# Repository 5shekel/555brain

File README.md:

555brain
========

555 based brain module

watch the video! > 

via http://www.reddit.com/r/electronics/comments/fsjno/simple_555_timer_based_servo_controllers_for/  
orginal design by Tom Jenner based on work by B.E.A.M robotics community and Mark Tilden et al

555brain thru-hole branch, cut on copper foil in TAMI.org.il

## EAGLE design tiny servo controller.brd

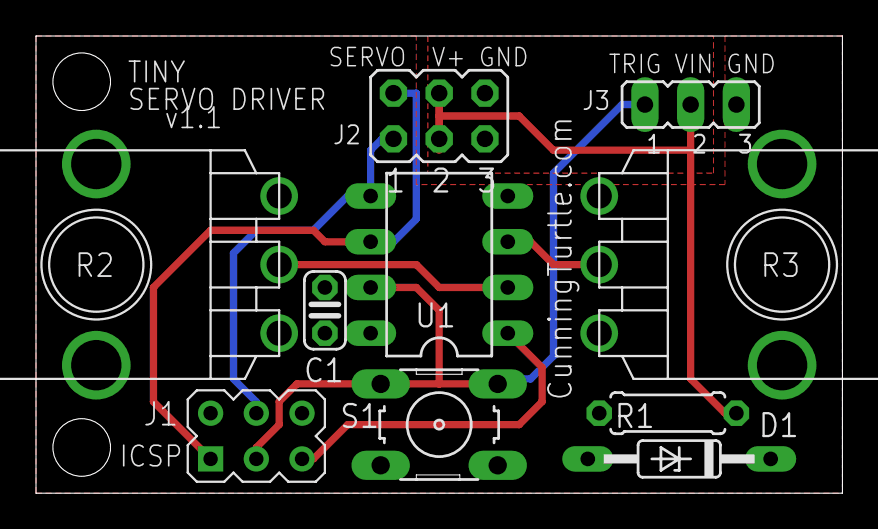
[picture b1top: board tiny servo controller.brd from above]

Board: 2 copper layers, 44.8 x 25.4 mm, 10 parts (0 on the bottom side), 9 nets.

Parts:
C1: 0.1uF; C025-024X044
D1: 5.1V; DO35Z10
J1: AVR_SPI_PRG; AVR_ISP_6P
J2: JP3Q
J3: JP2
R1: 33; 0207/7
R2, R3: CT2265-ND
S1: TACTILE_6MM
U1: ATTINY85DIL08; DIL08

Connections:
GND: C1.2, D1.A, J1.6, J2.5, J2.6, J3.3, R2.3, R3.3, S1.3, S1.4, U1.4
MISO/PWM2: J1.1, J2.2, U1.6
MOSI/PWM1: J1.4, J2.1, U1.5
POT1: R2.2, U1.2
POT2: R3.2, U1.3
RESET_N: J1.5, U1.1
SCK/SWITCH: J1.3, J3.1, S1.1, S1.2, U1.7
V+: J2.3, J2.4, J3.2, R1.1
VCC: C1.1, D1.C, J1.2, R1.2, R2.1, R3.1, U1.8

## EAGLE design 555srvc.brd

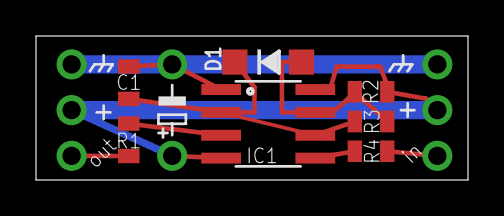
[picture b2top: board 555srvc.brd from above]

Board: 2 copper layers, 24.0 x 8.0 mm, 11 parts (1 on the bottom side), 8 nets.

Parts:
C1: 1uF; 0805
C2: E5-6
D1: SOD-123
IC1: 555; SO08
JP2: SERVO_OUT; 1X03-CLEANBIG
JP3: INPUT / CV; 1X03-CLEANBIG
R1: 2.2k; 0805
R2: 1.5k; 0805
R3: 47k; 0805
R4: 15k; 0805
U$5: OSHW_6X100_NOTEXT

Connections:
GND: C1.2, C2.-, IC1.1, JP2.1, JP3.1
INPUT: JP3.3, R4.2
unnamed: C1.1, D1.C, IC1.2, IC1.6, R3.1
unnamed: D1.A, IC1.7, R2.2, R3.2
unnamed: IC1.5, R4.1
unnamed: IC1.3, R1.1
SERVO_OUT: JP2.3, R1.2
VCC: C2.+, IC1.4, IC1.8, JP2.2, JP3.2, R2.1

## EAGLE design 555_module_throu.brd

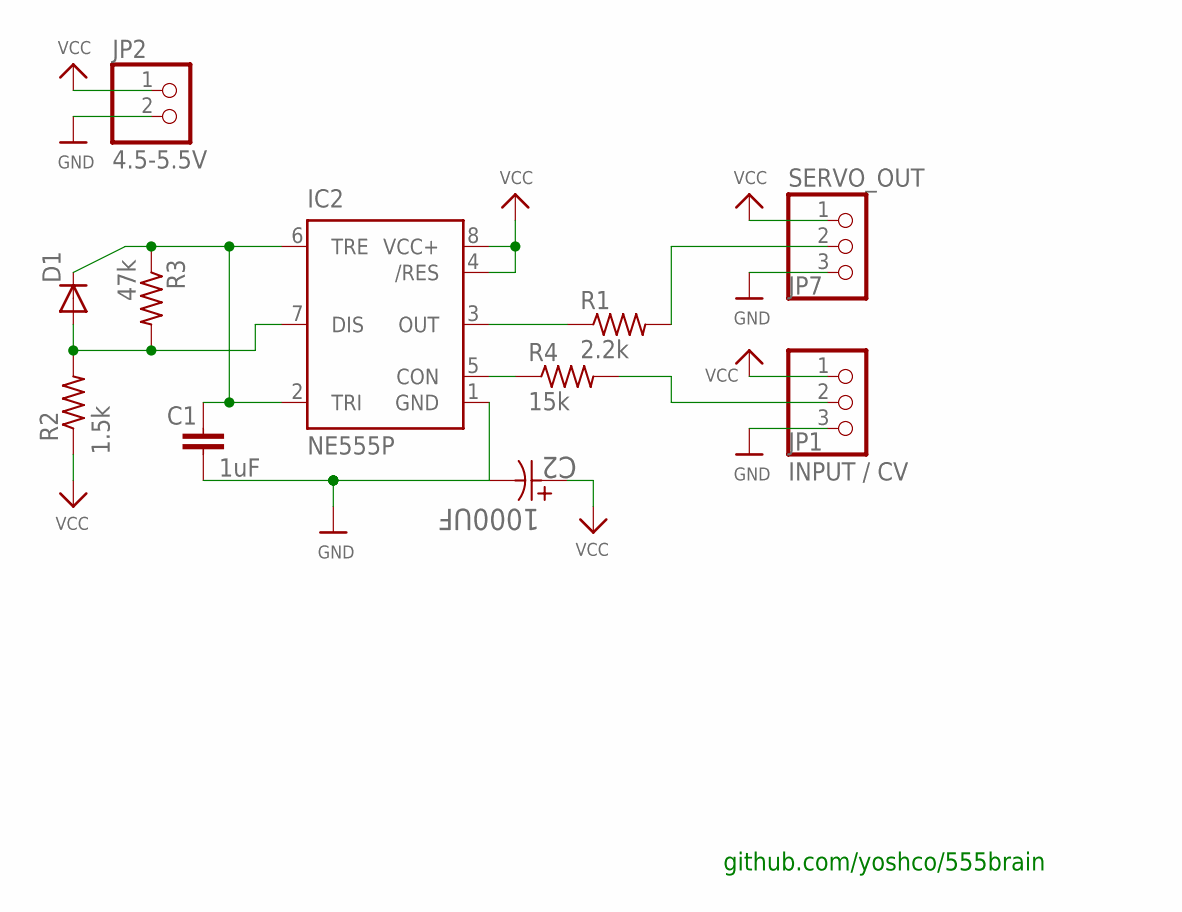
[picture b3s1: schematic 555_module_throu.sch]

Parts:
C1: 1uF; AXIAL-5MM
C2: 1000UF; CAPPR500-1000X3200
D1: 1N4004; DO41-10
IC2: NE555P; DIL-08
JP1: INPUT / CV; 1X03
JP2: 4.5-5.5V; 1X02_OVAL
JP7: SERVO_OUT; 1X03
R1: 2.2k; 0204/7
R2: 1.5k; 0204/7
R3: 47k; 0204/7
R4: 15k; 0204/7

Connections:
GND: C1.P$2 (2), C2.2, IC2.1 (GND), JP1.3, JP2.2, JP7.3
INPUT: JP1.2, R4.2
unnamed: C1.P$1 (1), D1.C, IC2.2 (TRI), IC2.6 (TRE), R3.1
unnamed: D1.A, IC2.7 (DIS), R2.2, R3.2
unnamed: IC2.5 (CON), R4.1
unnamed: IC2.3 (OUT), R1.1
SERVO_OUT: JP7.2, R1.2
VCC: C2.1, IC2.4 (/RES), IC2.8 (VCC+), JP1.1, JP2.1, JP7.1, R2.1

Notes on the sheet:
github.com/yoshco/555brain

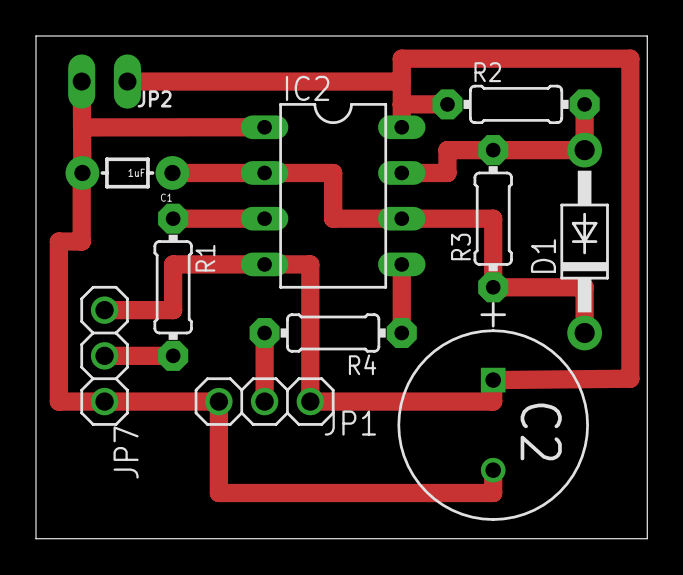
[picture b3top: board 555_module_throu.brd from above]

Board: 2 copper layers, 34.0 x 27.9 mm, 11 parts (0 on the bottom side), 8 nets.

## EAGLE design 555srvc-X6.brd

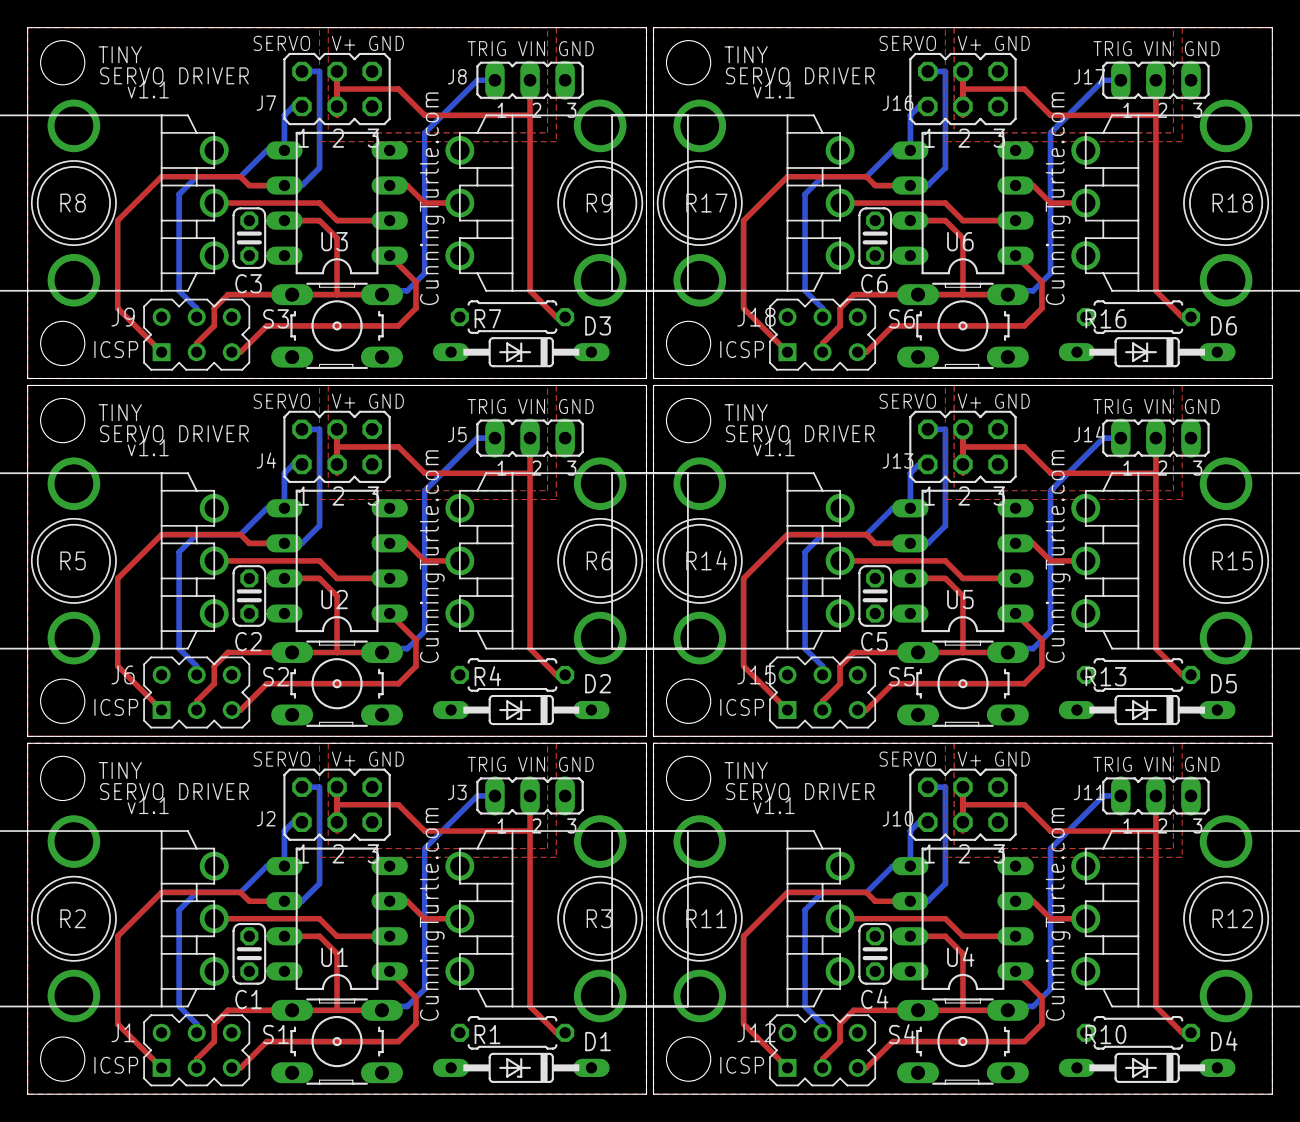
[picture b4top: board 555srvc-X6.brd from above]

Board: 2 copper layers, 90.1 x 77.2 mm, 60 parts (0 on the bottom side), 54 nets.

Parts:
C1, C2, C3, C4, C5, C6: 0.1uF; C025-024X044
D1, D2, D3, D4, D5, D6: 5.1V; DO35Z10
J1, J6, J9, J12, J15, J18: AVR_SPI_PRG; AVR_ISP_6P
J2, J4, J7, J10, J13, J16: JP3Q
J3, J5, J8, J11, J14, J17: JP2
R1, R4, R7, R10, R13, R16: 33; 0207/7
R2, R3, R5, R6, R8, R9, R11, R12, R14, R15, R17, R18: CT2265-ND
S1, S2, S3, S4, S5, S6: TACTILE_6MM
U1, U2, U3, U4, U5, U6: ATTINY85DIL08; DIL08

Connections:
GND: C1.2, D1.A, J1.6, J2.5, J2.6, J3.3, R2.3, R3.3, S1.3, S1.4, U1.4
GND1: C2.2, D2.A, J4.5, J4.6, J5.3, J6.6, R5.3, R6.3, S2.3, S2.4, U2.4
GND2: C3.2, D3.A, J7.5, J7.6, J8.3, J9.6, R8.3, R9.3, S3.3, S3.4, U3.4
GND3: C4.2, D4.A, J10.5, J10.6, J11.3, J12.6, R11.3, R12.3, S4.3, S4.4, U4.4
GND4: C5.2, D5.A, J13.5, J13.6, J14.3, J15.6, R14.3, R15.3, S5.3, S5.4, U5.4
GND5: C6.2, D6.A, J16.5, J16.6, J17.3, J18.6, R17.3, R18.3, S6.3, S6.4, U6.4
MISO/PWM1: J4.2, J6.1, U2.6
MISO/PWM2: J1.1, J2.2, U1.6
MISO/PWM3: J7.2, J9.1, U3.6
MISO/PWM4: J10.2, J12.1, U4.6
MISO/PWM5: J13.2, J15.1, U5.6
MISO/PWM6: J16.2, J18.1, U6.6
MOSI/PWM1: J1.4, J2.1, U1.5
MOSI/PWM2: J4.1, J6.4, U2.5
MOSI/PWM3: J7.1, J9.4, U3.5
MOSI/PWM4: J10.1, J12.4, U4.5
MOSI/PWM5: J13.1, J15.4, U5.5
MOSI/PWM6: J16.1, J18.4, U6.5
POT1: R2.2, U1.2
POT2: R3.2, U1.3
POT3: R5.2, U2.2
POT4: R6.2, U2.3
POT5: R8.2, U3.2
POT6: R9.2, U3.3
POT7: R11.2, U4.2
POT8: R12.2, U4.3
POT9: R14.2, U5.2
POT10: R15.2, U5.3
POT11: R17.2, U6.2
POT12: R18.2, U6.3
RESET_N: J1.5, U1.1
RESET_N1: J6.5, U2.1
RESET_N2: J9.5, U3.1
RESET_N3: J12.5, U4.1
RESET_N4: J15.5, U5.1
RESET_N5: J18.5, U6.1
SCK/SWITCH: J1.3, J3.1, S1.1, S1.2, U1.7
SCK/SWITCH1: J5.1, J6.3, S2.1, S2.2, U2.7
SCK/SWITCH2: J8.1, J9.3, S3.1, S3.2, U3.7
SCK/SWITCH3: J11.1, J12.3, S4.1, S4.2, U4.7
SCK/SWITCH4: J14.1, J15.3, S5.1, S5.2, U5.7
SCK/SWITCH5: J17.1, J18.3, S6.1, S6.2, U6.7
V+: J2.3, J2.4, J3.2, R1.1
V+1: J4.3, J4.4, J5.2, R4.1
V+2: J7.3, J7.4, J8.2, R7.1
V+3: J10.3, J10.4, J11.2, R10.1
V+4: J13.3, J13.4, J14.2, R13.1
V+5: J16.3, J16.4, J17.2, R16.1
VCC: C1.1, D1.C, J1.2, R1.2, R2.1, R3.1, U1.8
VCC1: C2.1, D2.C, J6.2, R4.2, R5.1, R6.1, U2.8
VCC2: C3.1, D3.C, J9.2, R7.2, R8.1, R9.1, U3.8
VCC3: C4.1, D4.C, J12.2, R10.2, R11.1, R12.1, U4.8
VCC4: C5.1, D5.C, J15.2, R13.2, R14.1, R15.1, U5.8
VCC5: C6.1, D6.C, J18.2, R16.2, R17.1, R18.1, U6.8

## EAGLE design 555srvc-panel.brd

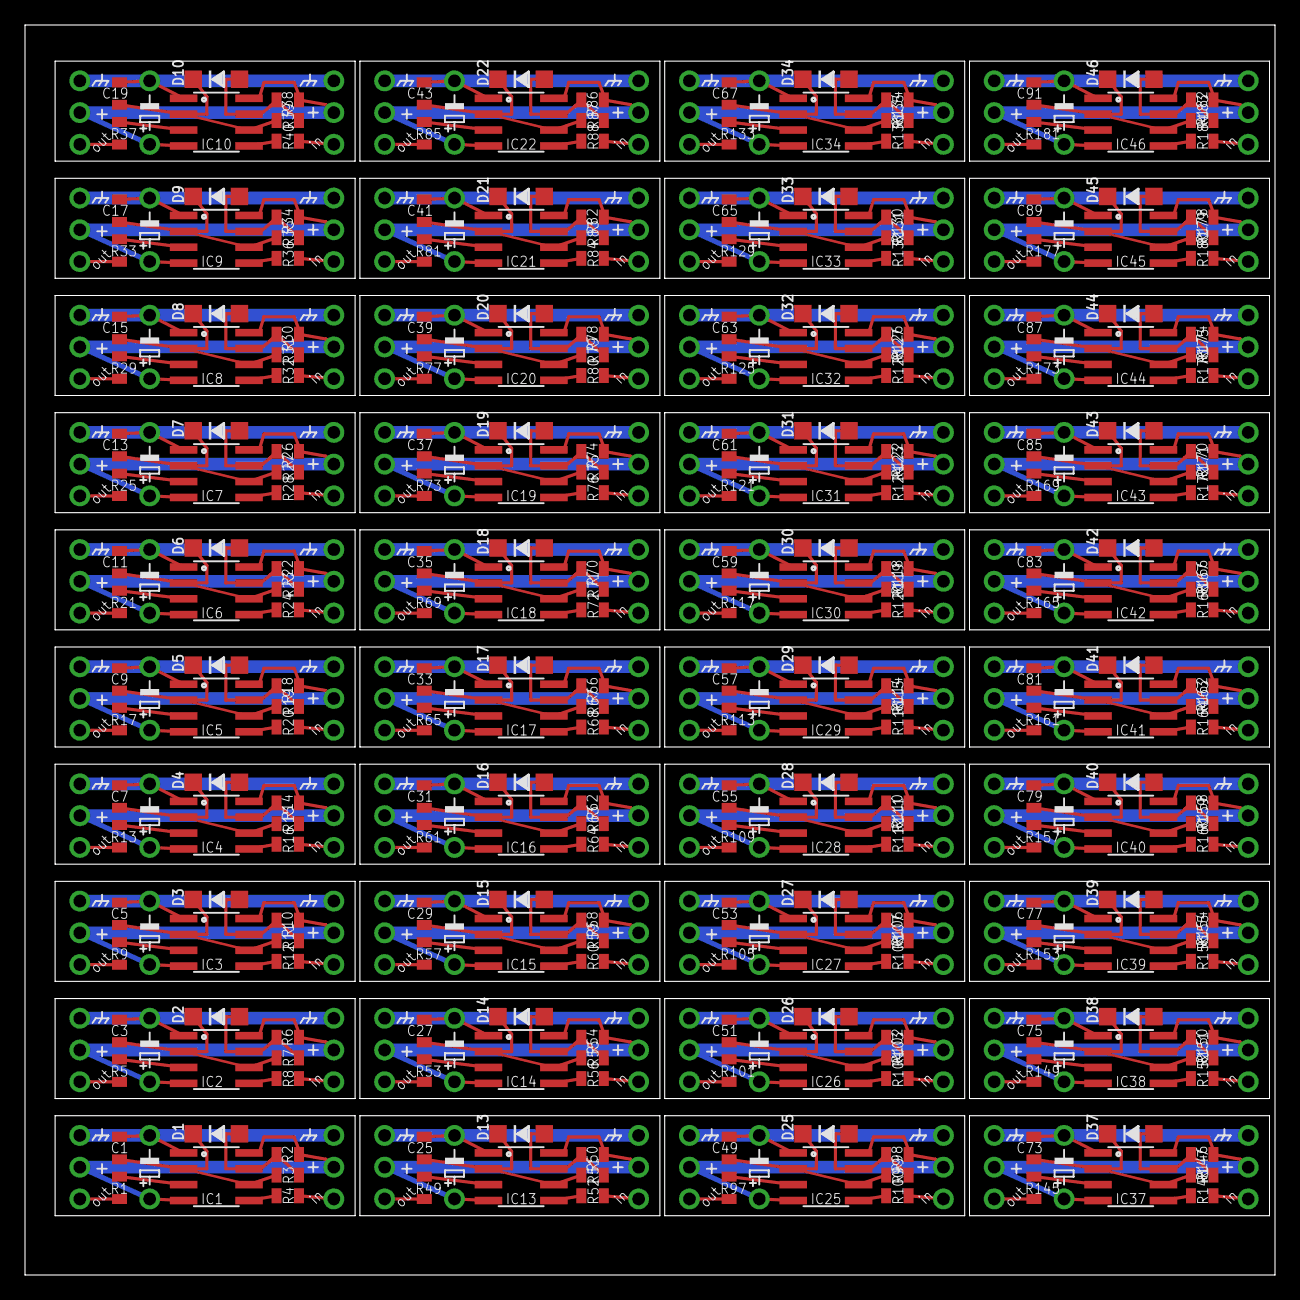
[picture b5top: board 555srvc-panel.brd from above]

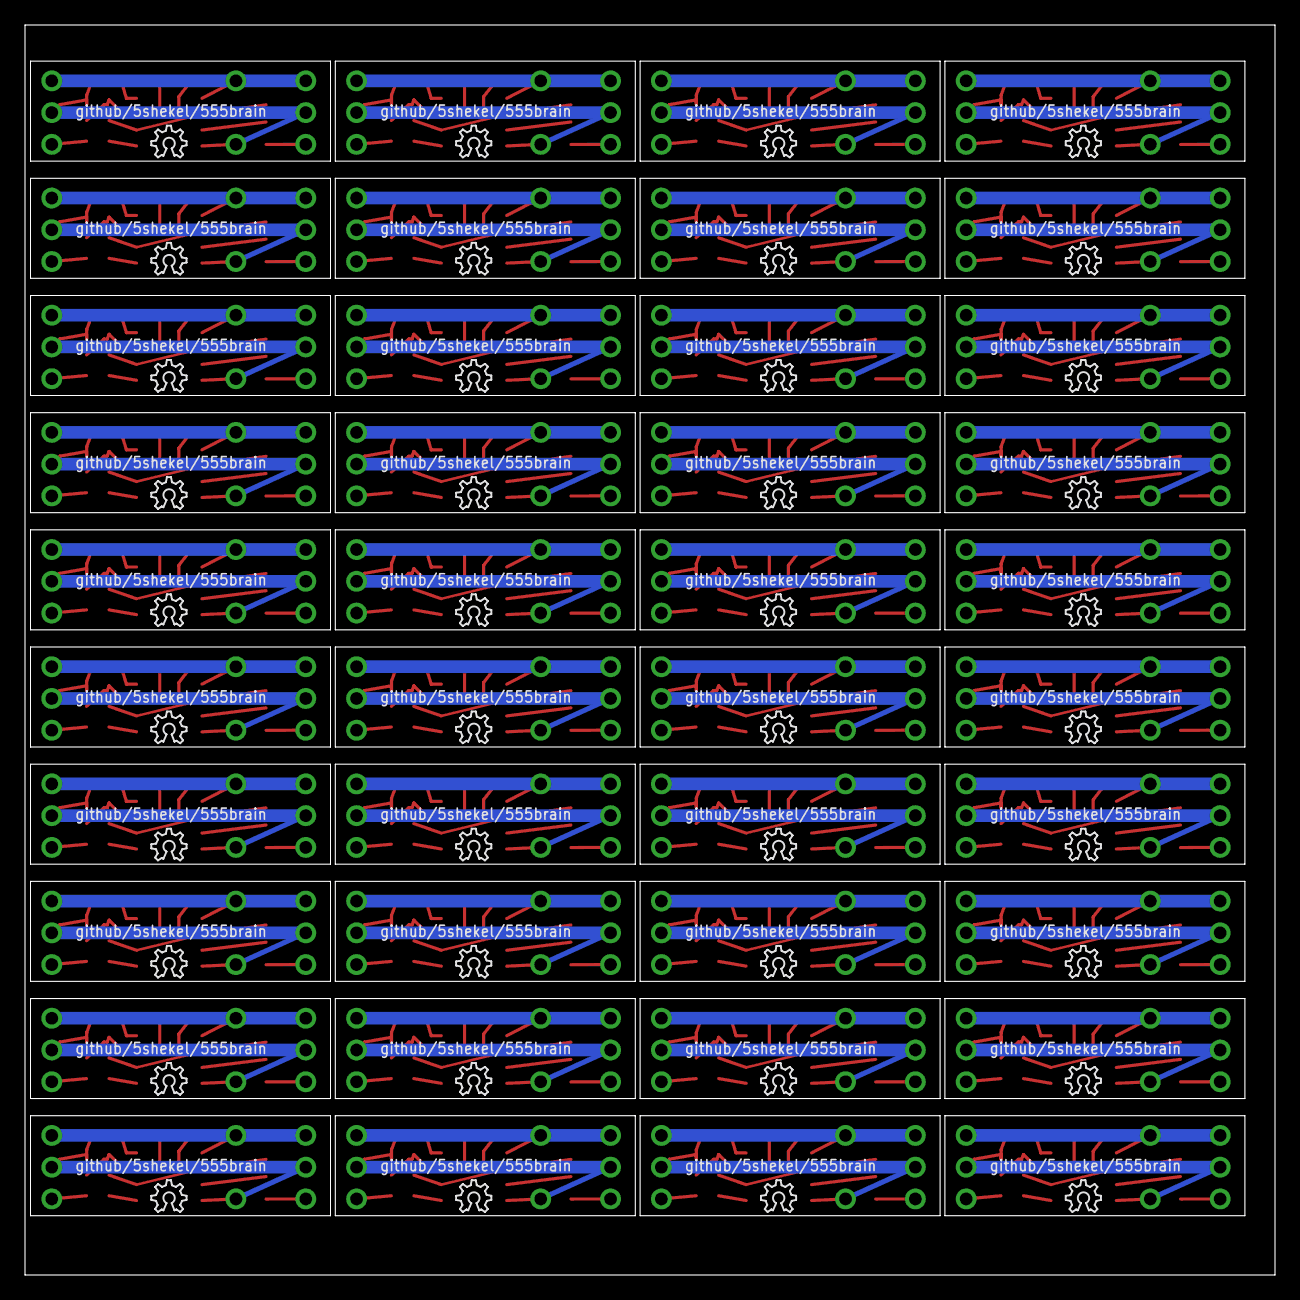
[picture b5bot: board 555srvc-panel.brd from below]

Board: 2 copper layers, 100.0 x 100.0 mm, 440 parts (40 on the bottom side), 320 nets.

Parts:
C1, C3, C5, C7, C9, C11, C13, C15, C17, C19, C25, C27, C29, C31, C33, C35, C37, C39, C41, C43, C49, C51, C53, C55, C57, C59, C61, C63, C65, C67, C73, C75, C77, C79, C81, C83, C85, C87, C89, C91: 1uF; 0805
C2, C4, C6, C8, C10, C12, C14, C16, C18, C20, C26, C28, C30, C32, C34, C36, C38, C40, C42, C44, C50, C52, C54, C56, C58, C60, C62, C64, C66, C68, C74, C76, C78, C80, C82, C84, C86, C88, C90, C92: E5-6
D1, D2, D3, D4, D5, D6, D7, D8, D9, D10, D13, D14, D15, D16, D17, D18, D19, D20, D21, D22, D25, D26, D27, D28, D29, D30, D31, D32, D33, D34, D37, D38, D39, D40, D41, D42, D43, D44, D45, D46: SOD-123
IC1, IC2, IC3, IC4, IC5, IC6, IC7, IC8, IC9, IC10, IC13, IC14, IC15, IC16, IC17, IC18, IC19, IC20, IC21, IC22, IC25, IC26, IC27, IC28, IC29, IC30, IC31, IC32, IC33, IC34, IC37, IC38, IC39, IC40, IC41, IC42, IC43, IC44, IC45, IC46: 555; SO08
JP1, JP2, JP5, JP7, JP9, JP11, JP13, JP15, JP17, JP19, JP25, JP27, JP29, JP31, JP33, JP35, JP37, JP39, JP41, JP43, JP49, JP51, JP53, JP55, JP57, JP59, JP61, JP63, JP65, JP67, JP73, JP75, JP77, JP79, JP81, JP83, JP85, JP87, JP89, JP91: SERVO_OUT; 1X03-CLEANBIG
JP3, JP4, JP6, JP8, JP10, JP12, JP14, JP16, JP18, JP20, JP26, JP28, JP30, JP32, JP34, JP36, JP38, JP40, JP42, JP44, JP50, JP52, JP54, JP56, JP58, JP60, JP62, JP64, JP66, JP68, JP74, JP76, JP78, JP80, JP82, JP84, JP86, JP88, JP90, JP92: INPUT / CV; 1X03-CLEANBIG
R1, R5, R9, R13, R17, R21, R25, R29, R33, R37, R49, R53, R57, R61, R65, R69, R73, R77, R81, R85, R97, R101, R105, R109, R113, R117, R121, R125, R129, R133, R145, R149, R153, R157, R161, R165, R169, R173, R177, R181: 2.2k; 0805
R2, R6, R10, R14, R18, R22, R26, R30, R34, R38, R50, R54, R58, R62, R66, R70, R74, R78, R82, R86, R98, R102, R106, R110, R114, R118, R122, R126, R130, R134, R146, R150, R154, R158, R162, R166, R170, R174, R178, R182: 1.5k; 0805
R3, R7, R11, R15, R19, R23, R27, R31, R35, R39, R51, R55, R59, R63, R67, R71, R75, R79, R83, R87, R99, R103, R107, R111, R115, R119, R123, R127, R131, R135, R147, R151, R155, R159, R163, R167, R171, R175, R179, R183: 47k; 0805
R4, R8, R12, R16, R20, R24, R28, R32, R36, R40, R52, R56, R60, R64, R68, R72, R76, R80, R84, R88, R100, R104, R108, R112, R116, R120, R124, R128, R132, R136, R148, R152, R156, R160, R164, R168, R172, R176, R180, R184: 15k; 0805
U$1, U$2, U$3, U$4, U$5, U$6, U$7, U$8, U$9, U$10, U$13, U$14, U$15, U$16, U$17, U$18, U$19, U$20, U$21, U$22, U$25, U$26, U$27, U$28, U$29, U$30, U$31, U$32, U$33, U$34, U$37, U$38, U$39, U$40, U$41, U$42, U$43, U$44, U$45, U$46: OSHW_6X100_NOTEXT

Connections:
GND: C1.2, C2.-, IC1.1, JP2.1, JP3.1
GND1: C3.2, C4.-, IC2.1, JP1.1, JP4.1
GND2: C5.2, C6.-, IC3.1, JP5.1, JP6.1
GND3: C7.2, C8.-, IC4.1, JP7.1, JP8.1
GND4: C9.2, C10.-, IC5.1, JP9.1, JP10.1
GND5: C11.2, C12.-, IC6.1, JP11.1, JP12.1
GND6: C13.2, C14.-, IC7.1, JP13.1, JP14.1
GND7: C15.2, C16.-, IC8.1, JP15.1, JP16.1
GND8: C17.2, C18.-, IC9.1, JP17.1, JP18.1
GND9: C19.2, C20.-, IC10.1, JP19.1, JP20.1
GND12: C25.2, C26.-, IC13.1, JP25.1, JP26.1
GND13: C27.2, C28.-, IC14.1, JP27.1, JP28.1
GND14: C29.2, C30.-, IC15.1, JP29.1, JP30.1
GND15: C31.2, C32.-, IC16.1, JP31.1, JP32.1
GND16: C33.2, C34.-, IC17.1, JP33.1, JP34.1
GND17: C35.2, C36.-, IC18.1, JP35.1, JP36.1
GND18: C37.2, C38.-, IC19.1, JP37.1, JP38.1
GND19: C39.2, C40.-, IC20.1, JP39.1, JP40.1
GND20: C41.2, C42.-, IC21.1, JP41.1, JP42.1
GND21: C43.2, C44.-, IC22.1, JP43.1, JP44.1
GND24: C49.2, C50.-, IC25.1, JP49.1, JP50.1
GND25: C51.2, C52.-, IC26.1, JP51.1, JP52.1
GND26: C53.2, C54.-, IC27.1, JP53.1, JP54.1
GND27: C55.2, C56.-, IC28.1, JP55.1, JP56.1
GND28: C57.2, C58.-, IC29.1, JP57.1, JP58.1
GND29: C59.2, C60.-, IC30.1, JP59.1, JP60.1
GND30: C61.2, C62.-, IC31.1, JP61.1, JP62.1
GND31: C63.2, C64.-, IC32.1, JP63.1, JP64.1
GND32: C65.2, C66.-, IC33.1, JP65.1, JP66.1
GND33: C67.2, C68.-, IC34.1, JP67.1, JP68.1
GND36: C73.2, C74.-, IC37.1, JP73.1, JP74.1
GND37: C75.2, C76.-, IC38.1, JP75.1, JP76.1
GND38: C77.2, C78.-, IC39.1, JP77.1, JP78.1
GND39: C79.2, C80.-, IC40.1, JP79.1, JP80.1
GND40: C81.2, C82.-, IC41.1, JP81.1, JP82.1
GND41: C83.2, C84.-, IC42.1, JP83.1, JP84.1
GND42: C85.2, C86.-, IC43.1, JP85.1, JP86.1
GND43: C87.2, C88.-, IC44.1, JP87.1, JP88.1
GND44: C89.2, C90.-, IC45.1, JP89.1, JP90.1
GND45: C91.2, C92.-, IC46.1, JP91.1, JP92.1
INPUT: JP3.3, R4.2
INPUT1: JP4.3, R8.2
INPUT2: JP6.3, R12.2
INPUT3: JP8.3, R16.2
INPUT4: JP10.3, R20.2
INPUT5: JP12.3, R24.2
INPUT6: JP14.3, R28.2
INPUT7: JP16.3, R32.2
INPUT8: JP18.3, R36.2
INPUT9: JP20.3, R40.2
INPUT12: JP26.3, R52.2
INPUT13: JP28.3, R56.2
INPUT14: JP30.3, R60.2
INPUT15: JP32.3, R64.2
INPUT16: JP34.3, R68.2
INPUT17: JP36.3, R72.2
INPUT18: JP38.3, R76.2
INPUT19: JP40.3, R80.2
INPUT20: JP42.3, R84.2
INPUT21: JP44.3, R88.2
INPUT24: JP50.3, R100.2
INPUT25: JP52.3, R104.2
INPUT26: JP54.3, R108.2
INPUT27: JP56.3, R112.2
INPUT28: JP58.3, R116.2
INPUT29: JP60.3, R120.2
INPUT30: JP62.3, R124.2
INPUT31: JP64.3, R128.2
INPUT32: JP66.3, R132.2
INPUT33: JP68.3, R136.2
INPUT36: JP74.3, R148.2
INPUT37: JP76.3, R152.2
INPUT38: JP78.3, R156.2
INPUT39: JP80.3, R160.2
INPUT40: JP82.3, R164.2
INPUT41: JP84.3, R168.2
INPUT42: JP86.3, R172.2
INPUT43: JP88.3, R176.2
INPUT44: JP90.3, R180.2
INPUT45: JP92.3, R184.2
unnamed: C1.1, D1.C, IC1.2, IC1.6, R3.1
unnamed: D1.A, IC1.7, R2.2, R3.2
unnamed: C3.1, D2.C, IC2.2, IC2.6, R7.1
unnamed: IC1.5, R4.1
unnamed: IC1.3, R1.1
unnamed: D2.A, IC2.7, R6.2, R7.2
unnamed: IC2.5, R8.1
unnamed: IC2.3, R5.1
unnamed: C5.1, D3.C, IC3.2, IC3.6, R11.1
unnamed: D3.A, IC3.7, R10.2, R11.2
unnamed: IC3.5, R12.1
unnamed: IC3.3, R9.1
unnamed: C7.1, D4.C, IC4.2, IC4.6, R15.1
unnamed: D4.A, IC4.7, R14.2, R15.2
unnamed: IC4.5, R16.1
unnamed: IC4.3, R13.1
unnamed: C9.1, D5.C, IC5.2, IC5.6, R19.1
unnamed: D5.A, IC5.7, R18.2, R19.2
unnamed: IC5.5, R20.1
unnamed: IC5.3, R17.1
unnamed: C11.1, D6.C, IC6.2, IC6.6, R23.1
unnamed: D6.A, IC6.7, R22.2, R23.2
unnamed: IC6.5, R24.1
unnamed: IC6.3, R21.1
unnamed: C13.1, D7.C, IC7.2, IC7.6, R27.1
unnamed: D7.A, IC7.7, R26.2, R27.2
unnamed: IC7.5, R28.1
unnamed: IC7.3, R25.1
unnamed: C15.1, D8.C, IC8.2, IC8.6, R31.1
unnamed: D8.A, IC8.7, R30.2, R31.2
unnamed: IC8.5, R32.1
unnamed: IC8.3, R29.1
unnamed: C17.1, D9.C, IC9.2, IC9.6, R35.1
unnamed: D9.A, IC9.7, R34.2, R35.2
unnamed: IC9.5, R36.1
unnamed: IC9.3, R33.1
unnamed: C19.1, D10.C, IC10.2, IC10.6, R39.1
unnamed: D10.A, IC10.7, R38.2, R39.2
unnamed: IC10.5, R40.1
unnamed: IC10.3, R37.1
unnamed: C25.1, D13.C, IC13.2, IC13.6, R51.1
unnamed: D13.A, IC13.7, R50.2, R51.2
unnamed: IC13.5, R52.1
unnamed: IC13.3, R49.1
unnamed: C27.1, D14.C, IC14.2, IC14.6, R55.1
unnamed: D14.A, IC14.7, R54.2, R55.2
unnamed: IC14.5, R56.1
unnamed: IC14.3, R53.1
unnamed: C29.1, D15.C, IC15.2, IC15.6, R59.1
unnamed: D15.A, IC15.7, R58.2, R59.2
unnamed: IC15.5, R60.1
unnamed: IC15.3, R57.1
unnamed: C31.1, D16.C, IC16.2, IC16.6, R63.1
unnamed: D16.A, IC16.7, R62.2, R63.2
unnamed: IC16.5, R64.1
unnamed: IC16.3, R61.1
unnamed: C33.1, D17.C, IC17.2, IC17.6, R67.1
unnamed: D17.A, IC17.7, R66.2, R67.2
unnamed: IC17.5, R68.1
unnamed: IC17.3, R65.1
unnamed: C35.1, D18.C, IC18.2, IC18.6, R71.1
unnamed: D18.A, IC18.7, R70.2, R71.2
unnamed: IC18.5, R72.1
unnamed: IC18.3, R69.1
unnamed: C37.1, D19.C, IC19.2, IC19.6, R75.1
unnamed: D19.A, IC19.7, R74.2, R75.2
unnamed: IC19.5, R76.1
unnamed: IC19.3, R73.1
unnamed: C39.1, D20.C, IC20.2, IC20.6, R79.1
unnamed: D20.A, IC20.7, R78.2, R79.2
unnamed: IC20.5, R80.1
unnamed: IC20.3, R77.1
unnamed: C41.1, D21.C, IC21.2, IC21.6, R83.1
unnamed: D21.A, IC21.7, R82.2, R83.2
unnamed: IC21.5, R84.1
unnamed: IC21.3, R81.1
unnamed: C43.1, D22.C, IC22.2, IC22.6, R87.1
unnamed: D22.A, IC22.7, R86.2, R87.2
unnamed: IC22.5, R88.1
unnamed: IC22.3, R85.1
unnamed: C49.1, D25.C, IC25.2, IC25.6, R99.1
unnamed: D25.A, IC25.7, R98.2, R99.2
unnamed: IC25.5, R100.1
unnamed: IC25.3, R97.1
unnamed: C51.1, D26.C, IC26.2, IC26.6, R103.1
unnamed: D26.A, IC26.7, R102.2, R103.2
unnamed: IC26.5, R104.1
unnamed: IC26.3, R101.1
unnamed: C53.1, D27.C, IC27.2, IC27.6, R107.1
unnamed: D27.A, IC27.7, R106.2, R107.2
unnamed: IC27.5, R108.1
unnamed: IC27.3, R105.1
unnamed: C55.1, D28.C, IC28.2, IC28.6, R111.1
unnamed: D28.A, IC28.7, R110.2, R111.2
unnamed: IC28.5, R112.1
unnamed: IC28.3, R109.1
unnamed: C57.1, D29.C, IC29.2, IC29.6, R115.1
unnamed: D29.A, IC29.7, R114.2, R115.2
unnamed: IC29.5, R116.1
unnamed: IC29.3, R113.1
unnamed: C59.1, D30.C, IC30.2, IC30.6, R119.1
unnamed: D30.A, IC30.7, R118.2, R119.2
unnamed: IC30.5, R120.1
unnamed: IC30.3, R117.1
unnamed: C61.1, D31.C, IC31.2, IC31.6, R123.1
unnamed: D31.A, IC31.7, R122.2, R123.2
unnamed: IC31.5, R124.1
unnamed: IC31.3, R121.1
unnamed: C63.1, D32.C, IC32.2, IC32.6, R127.1
unnamed: D32.A, IC32.7, R126.2, R127.2
unnamed: IC32.5, R128.1
unnamed: IC32.3, R125.1
unnamed: C65.1, D33.C, IC33.2, IC33.6, R131.1
unnamed: D33.A, IC33.7, R130.2, R131.2
unnamed: IC33.5, R132.1
unnamed: IC33.3, R129.1
unnamed: C67.1, D34.C, IC34.2, IC34.6, R135.1
unnamed: D34.A, IC34.7, R134.2, R135.2
unnamed: IC34.5, R136.1
unnamed: IC34.3, R133.1
unnamed: C73.1, D37.C, IC37.2, IC37.6, R147.1
unnamed: D37.A, IC37.7, R146.2, R147.2
unnamed: IC37.5, R148.1
unnamed: IC37.3, R145.1
unnamed: C75.1, D38.C, IC38.2, IC38.6, R151.1
unnamed: D38.A, IC38.7, R150.2, R151.2
unnamed: IC38.5, R152.1
unnamed: IC38.3, R149.1
unnamed: C77.1, D39.C, IC39.2, IC39.6, R155.1
unnamed: D39.A, IC39.7, R154.2, R155.2
unnamed: IC39.5, R156.1
unnamed: IC39.3, R153.1
unnamed: C79.1, D40.C, IC40.2, IC40.6, R159.1
unnamed: D40.A, IC40.7, R158.2, R159.2
unnamed: IC40.5, R160.1
unnamed: IC40.3, R157.1
unnamed: C81.1, D41.C, IC41.2, IC41.6, R163.1
unnamed: D41.A, IC41.7, R162.2, R163.2
unnamed: IC41.5, R164.1
unnamed: IC41.3, R161.1
unnamed: C83.1, D42.C, IC42.2, IC42.6, R167.1
unnamed: D42.A, IC42.7, R166.2, R167.2
unnamed: IC42.5, R168.1
unnamed: IC42.3, R165.1
unnamed: C85.1, D43.C, IC43.2, IC43.6, R171.1
unnamed: D43.A, IC43.7, R170.2, R171.2
unnamed: IC43.5, R172.1
unnamed: IC43.3, R169.1
unnamed: C87.1, D44.C, IC44.2, IC44.6, R175.1
unnamed: D44.A, IC44.7, R174.2, R175.2
unnamed: IC44.5, R176.1
unnamed: IC44.3, R173.1
unnamed: C89.1, D45.C, IC45.2, IC45.6, R179.1
unnamed: D45.A, IC45.7, R178.2, R179.2
unnamed: IC45.5, R180.1
unnamed: IC45.3, R177.1
unnamed: C91.1, D46.C, IC46.2, IC46.6, R183.1
unnamed: D46.A, IC46.7, R182.2, R183.2
unnamed: IC46.5, R184.1
unnamed: IC46.3, R181.1
SERVO_OUT: JP2.3, R1.2
SERVO_OUT1: JP1.3, R5.2
SERVO_OUT2: JP5.3, R9.2
SERVO_OUT3: JP7.3, R13.2
SERVO_OUT4: JP9.3, R17.2
SERVO_OUT5: JP11.3, R21.2
SERVO_OUT6: JP13.3, R25.2
SERVO_OUT7: JP15.3, R29.2
SERVO_OUT8: JP17.3, R33.2
SERVO_OUT9: JP19.3, R37.2
SERVO_OUT12: JP25.3, R49.2
SERVO_OUT13: JP27.3, R53.2
SERVO_OUT14: JP29.3, R57.2
SERVO_OUT15: JP31.3, R61.2
SERVO_OUT16: JP33.3, R65.2
SERVO_OUT17: JP35.3, R69.2
SERVO_OUT18: JP37.3, R73.2
SERVO_OUT19: JP39.3, R77.2
SERVO_OUT20: JP41.3, R81.2
SERVO_OUT21: JP43.3, R85.2
SERVO_OUT24: JP49.3, R97.2
SERVO_OUT25: JP51.3, R101.2
SERVO_OUT26: JP53.3, R105.2
SERVO_OUT27: JP55.3, R109.2
SERVO_OUT28: JP57.3, R113.2
SERVO_OUT29: JP59.3, R117.2
SERVO_OUT30: JP61.3, R121.2
SERVO_OUT31: JP63.3, R125.2
SERVO_OUT32: JP65.3, R129.2
SERVO_OUT33: JP67.3, R133.2
SERVO_OUT36: JP73.3, R145.2
SERVO_OUT37: JP75.3, R149.2
SERVO_OUT38: JP77.3, R153.2
SERVO_OUT39: JP79.3, R157.2
SERVO_OUT40: JP81.3, R161.2
SERVO_OUT41: JP83.3, R165.2
SERVO_OUT42: JP85.3, R169.2
SERVO_OUT43: JP87.3, R173.2
SERVO_OUT44: JP89.3, R177.2
SERVO_OUT45: JP91.3, R181.2
VCC: C2.+, IC1.4, IC1.8, JP2.2, JP3.2, R2.1
VCC1: C4.+, IC2.4, IC2.8, JP1.2, JP4.2, R6.1
VCC2: C6.+, IC3.4, IC3.8, JP5.2, JP6.2, R10.1
VCC3: C8.+, IC4.4, IC4.8, JP7.2, JP8.2, R14.1
VCC4: C10.+, IC5.4, IC5.8, JP9.2, JP10.2, R18.1
VCC5: C12.+, IC6.4, IC6.8, JP11.2, JP12.2, R22.1
VCC6: C14.+, IC7.4, IC7.8, JP13.2, JP14.2, R26.1
VCC7: C16.+, IC8.4, IC8.8, JP15.2, JP16.2, R30.1
VCC8: C18.+, IC9.4, IC9.8, JP17.2, JP18.2, R34.1
VCC9: C20.+, IC10.4, IC10.8, JP19.2, JP20.2, R38.1
VCC12: C26.+, IC13.4, IC13.8, JP25.2, JP26.2, R50.1
VCC13: C28.+, IC14.4, IC14.8, JP27.2, JP28.2, R54.1
VCC14: C30.+, IC15.4, IC15.8, JP29.2, JP30.2, R58.1
VCC15: C32.+, IC16.4, IC16.8, JP31.2, JP32.2, R62.1
VCC16: C34.+, IC17.4, IC17.8, JP33.2, JP34.2, R66.1
VCC17: C36.+, IC18.4, IC18.8, JP35.2, JP36.2, R70.1
VCC18: C38.+, IC19.4, IC19.8, JP37.2, JP38.2, R74.1
VCC19: C40.+, IC20.4, IC20.8, JP39.2, JP40.2, R78.1
VCC20: C42.+, IC21.4, IC21.8, JP41.2, JP42.2, R82.1
VCC21: C44.+, IC22.4, IC22.8, JP43.2, JP44.2, R86.1
VCC24: C50.+, IC25.4, IC25.8, JP49.2, JP50.2, R98.1
VCC25: C52.+, IC26.4, IC26.8, JP51.2, JP52.2, R102.1
VCC26: C54.+, IC27.4, IC27.8, JP53.2, JP54.2, R106.1
VCC27: C56.+, IC28.4, IC28.8, JP55.2, JP56.2, R110.1
VCC28: C58.+, IC29.4, IC29.8, JP57.2, JP58.2, R114.1
VCC29: C60.+, IC30.4, IC30.8, JP59.2, JP60.2, R118.1
VCC30: C62.+, IC31.4, IC31.8, JP61.2, JP62.2, R122.1
VCC31: C64.+, IC32.4, IC32.8, JP63.2, JP64.2, R126.1
VCC32: C66.+, IC33.4, IC33.8, JP65.2, JP66.2, R130.1
VCC33: C68.+, IC34.4, IC34.8, JP67.2, JP68.2, R134.1
VCC36: C74.+, IC37.4, IC37.8, JP73.2, JP74.2, R146.1
VCC37: C76.+, IC38.4, IC38.8, JP75.2, JP76.2, R150.1
VCC38: C78.+, IC39.4, IC39.8, JP77.2, JP78.2, R154.1
VCC39: C80.+, IC40.4, IC40.8, JP79.2, JP80.2, R158.1
VCC40: C82.+, IC41.4, IC41.8, JP81.2, JP82.2, R162.1
VCC41: C84.+, IC42.4, IC42.8, JP83.2, JP84.2, R166.1
VCC42: C86.+, IC43.4, IC43.8, JP85.2, JP86.2, R170.1
VCC43: C88.+, IC44.4, IC44.8, JP87.2, JP88.2, R174.1
VCC44: C90.+, IC45.4, IC45.8, JP89.2, JP90.2, R178.1
VCC45: C92.+, IC46.4, IC46.8, JP91.2, JP92.2, R182.1

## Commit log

2014-10-20 :space_invader: Added .gitattributes & .gitignore files
2014-10-20 an eagle version of the 555 brain
    via
    http://www.reddit.com/r/electronics/comments/fsjno/simple_555_timer_based_servo_controllers_for/
2014-10-20 Create gh-pages branch via GitHub
2014-10-20 added frame
2014-10-20 schema
2014-10-21 papercut sessions
    added files used in generating paper cut
    https://www.youtube.com/watch?v=Gg8W51C2M4U
2015-10-06 smd is go
2015-10-06 crucial wiring change for standard servo wiring on JP1 and JP2
2015-10-07 smd added schema and board pdf,png
2015-10-07 added 555srvc.png which is a corrected version of the gif, with the 555 pin 1 cross conected
2015-10-07 added size to brd png
2015-10-13 smd wip
2015-10-13 board layout
2015-10-14 added lib with all parts
2015-10-14 all devices moved to the 555brain lib
2015-10-14 looks legit
2015-10-14 changes pintout to coform with servo out.
2015-10-14 new brd layout pic
2015-10-14 gitignore correction and new ver from smd
2015-10-14 added symbols for in/out and updated lib for capacitor pakcge
2015-10-15 update pic, and sorted silkscreen
2015-10-15 new layout
2015-10-17 fat traces to output
2015-10-21 rotated a resistor
2015-10-22 attiny85 ver
2015-10-23 before panel
2015-10-24 new dim 23x8mm
2015-10-24 added Bname
2015-10-24 added OHW logo
2015-10-24 sent to fab- panelized 4x10
2015-10-25 nice pics
2015-10-25 added tiny servo controler and gerber panelize
2015-11-28 added legend

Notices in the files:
parts and their libraries:
SparkFun-Capacitors: Licensing: CC v3.0 Share-Alike You are welcome to use this library for commercial purposes.
microbuilder: This work is placed in the public domain, and may be freely used for commercial and non-commercial work with the following conditions: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
